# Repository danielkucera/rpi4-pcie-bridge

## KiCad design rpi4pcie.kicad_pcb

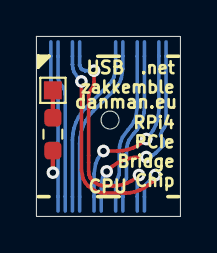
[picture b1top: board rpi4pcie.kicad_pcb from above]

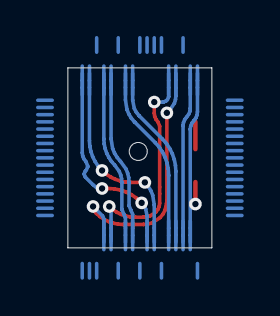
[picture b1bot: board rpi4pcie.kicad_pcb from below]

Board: 2 copper layers, 8.0 x 10.0 mm, 89 parts (88 on the bottom side), 10 nets.

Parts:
@HOLE0: (no value)
PAD1, PAD2, PAD3, PAD4, PAD5, PAD6, PAD7, PAD8, PAD9, PAD10, PAD11, PAD12, PAD13, PAD14, PAD15, PAD16, PAD17, PAD18, PAD19, PAD20, PAD21, PAD22, PAD23, PAD24, PAD25, PAD26, PAD27, PAD28, PAD29, PAD30, PAD31, PAD32, PAD33, PAD34, PAD35, PAD36, PAD37, PAD38, PAD39, PAD40, PAD41, PAD42, PAD43, PAD44, PAD45, PAD46, PAD47, PAD48, PAD49, PAD50, PAD51, PAD52, PAD53, PAD54, PAD55, PAD56, PAD57, PAD58, PAD59, PAD60, PAD61, PAD62, PAD63, PAD64, PAD65, PAD66, PAD67, PAD68, PAD69, PAD70, PAD71, PAD72, PAD73, PAD74, PAD75, PAD76, PAD77, PAD78, PAD79, PAD80, PAD81, PAD82, PAD83, PAD84, PAD85, PAD86, PAD87, PAD88: PADQFN-0.4; PAD-QFN-0.4

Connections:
unnamed: PAD19.1, PAD68.1, PAD69.1, PAD77.1
unnamed: PAD20.1, PAD67.1, PAD70.1, PAD78.1
unnamed: PAD21.1, PAD59.1, PAD71.1, PAD79.1
unnamed: PAD22.1, PAD58.1, PAD72.1, PAD80.1
unnamed: PAD25.1, PAD52.1, PAD76.1, PAD82.1
unnamed: PAD31.1, PAD65.1, PAD86.1, PAD87.1
unnamed: PAD27.1, PAD56.1, PAD73.1, PAD83.1
unnamed: PAD28.1, PAD55.1, PAD74.1, PAD84.1
unnamed: PAD24.1, PAD53.1, PAD75.1, PAD81.1
unnamed: PAD30.1, PAD64.1, PAD85.1, PAD88.1
